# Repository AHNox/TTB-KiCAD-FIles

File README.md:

# TTB-KiCAD-FIles
This repository holds the KiCAD files for the Tidy Bowl Project

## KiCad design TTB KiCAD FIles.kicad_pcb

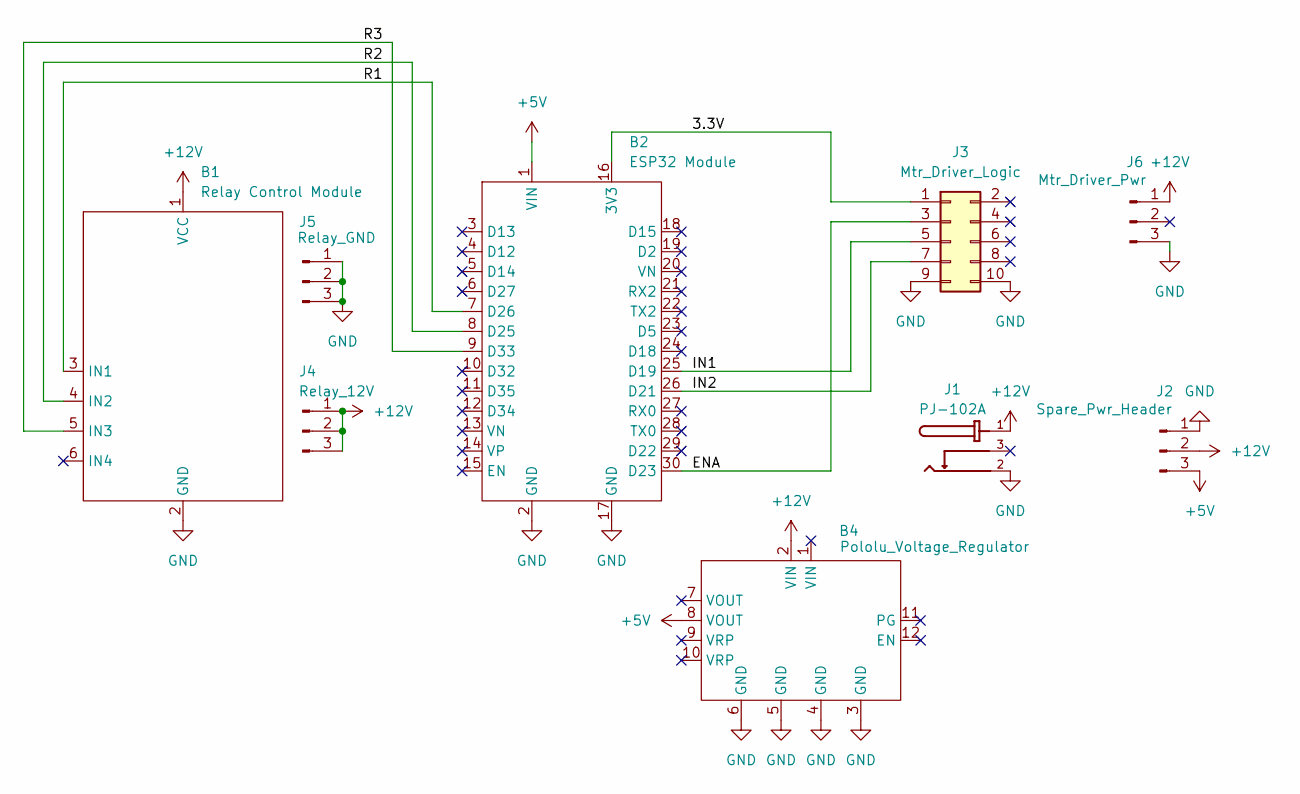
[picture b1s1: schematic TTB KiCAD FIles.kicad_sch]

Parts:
B1: Relay Control Module; 4 Relay Module
B2: ESP32 Module; ESP32_DEVKIT_V1_TYPE_C
B4: Pololu_Voltage_Regulator; Pololu Voltage Regulator
J1: PJ-102A; CUI_PJ-102A
J2: Spare_Pwr_Header; PinHeader_1x03_P2.54mm_Vertical
J3: Mtr_Driver_Logic; PinHeader_2x05_P2.54mm_Vertical
J4: Relay_12V; PinHeader_1x03_P2.54mm_Vertical
J5: Relay_GND; PinHeader_1x03_P2.54mm_Vertical
J6: Mtr_Driver_Pwr; PinHeader_1x03_P2.54mm_Vertical

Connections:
+5V: B2.1 (VIN), B4.8 (VOUT), J2.3
+12V: B1.1 (VCC), B4.2 (VIN), J1.1, J2.2, J4.1, J4.2, J4.3, J6.1
/3.3V: B2.16 (3V3), J3.1
/ENA: B2.30 (D23), J3.3
/IN1: B2.25 (D19), J3.5
/IN2: B2.26 (D21), J3.7
/R1: B1.3 (IN1), B2.7 (D26)
/R2: B1.4 (IN2), B2.8 (D25)
/R3: B1.5 (IN3), B2.9 (D33)
GND: B1.2 (GND), B2.2 (GND), B2.17 (GND), B4.3 (GND), B4.4 (GND), B4.5 (GND), B4.6 (GND), J1.2, J2.1, J3.9, J3.10, J5.1, J5.2, J5.3, J6.3

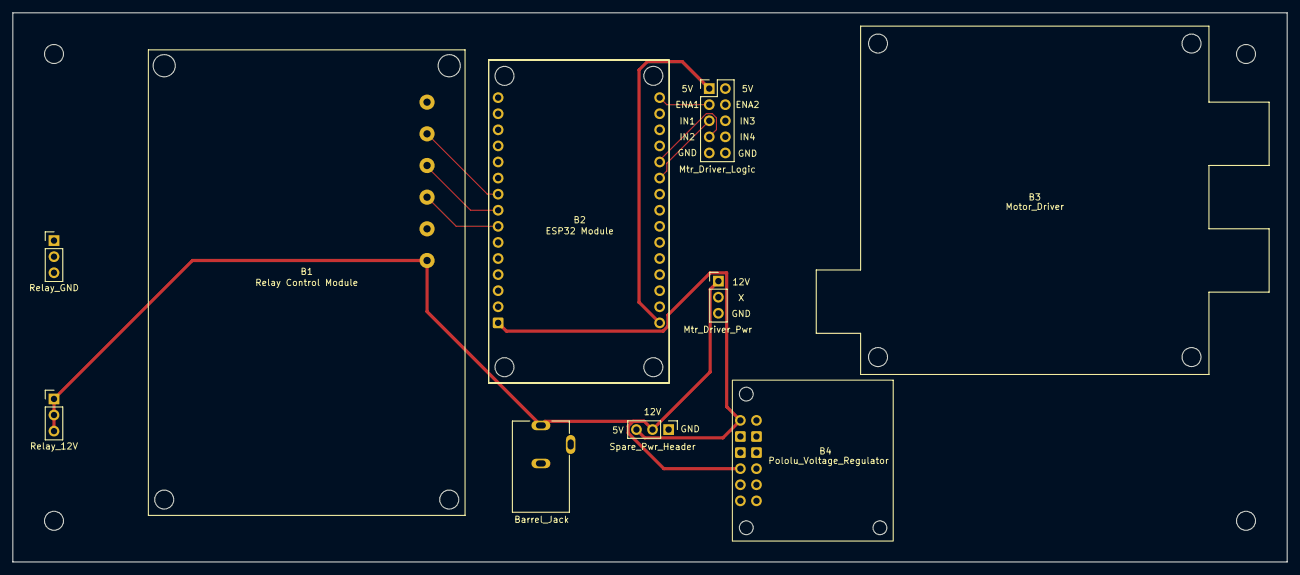
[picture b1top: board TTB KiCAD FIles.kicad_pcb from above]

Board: 2 copper layers, 201.2 x 86.7 mm, 10 parts (0 on the bottom side), 10 nets.

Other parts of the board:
B3: Motor_Driver; XY-160D Motor Driver

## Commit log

2025-04-28 Load files into repository
2025-05-05 Add draw.io block diagram
2025-05-07 Add component data sheets
2025-05-12 Added Design Modifications
2025-05-14 Clean up track wiring & add silkscreen clarification
2025-05-14 Add Wiring Diagram
2025-05-14 Clean up draw.io files & kicad files
2025-05-29 File backup
